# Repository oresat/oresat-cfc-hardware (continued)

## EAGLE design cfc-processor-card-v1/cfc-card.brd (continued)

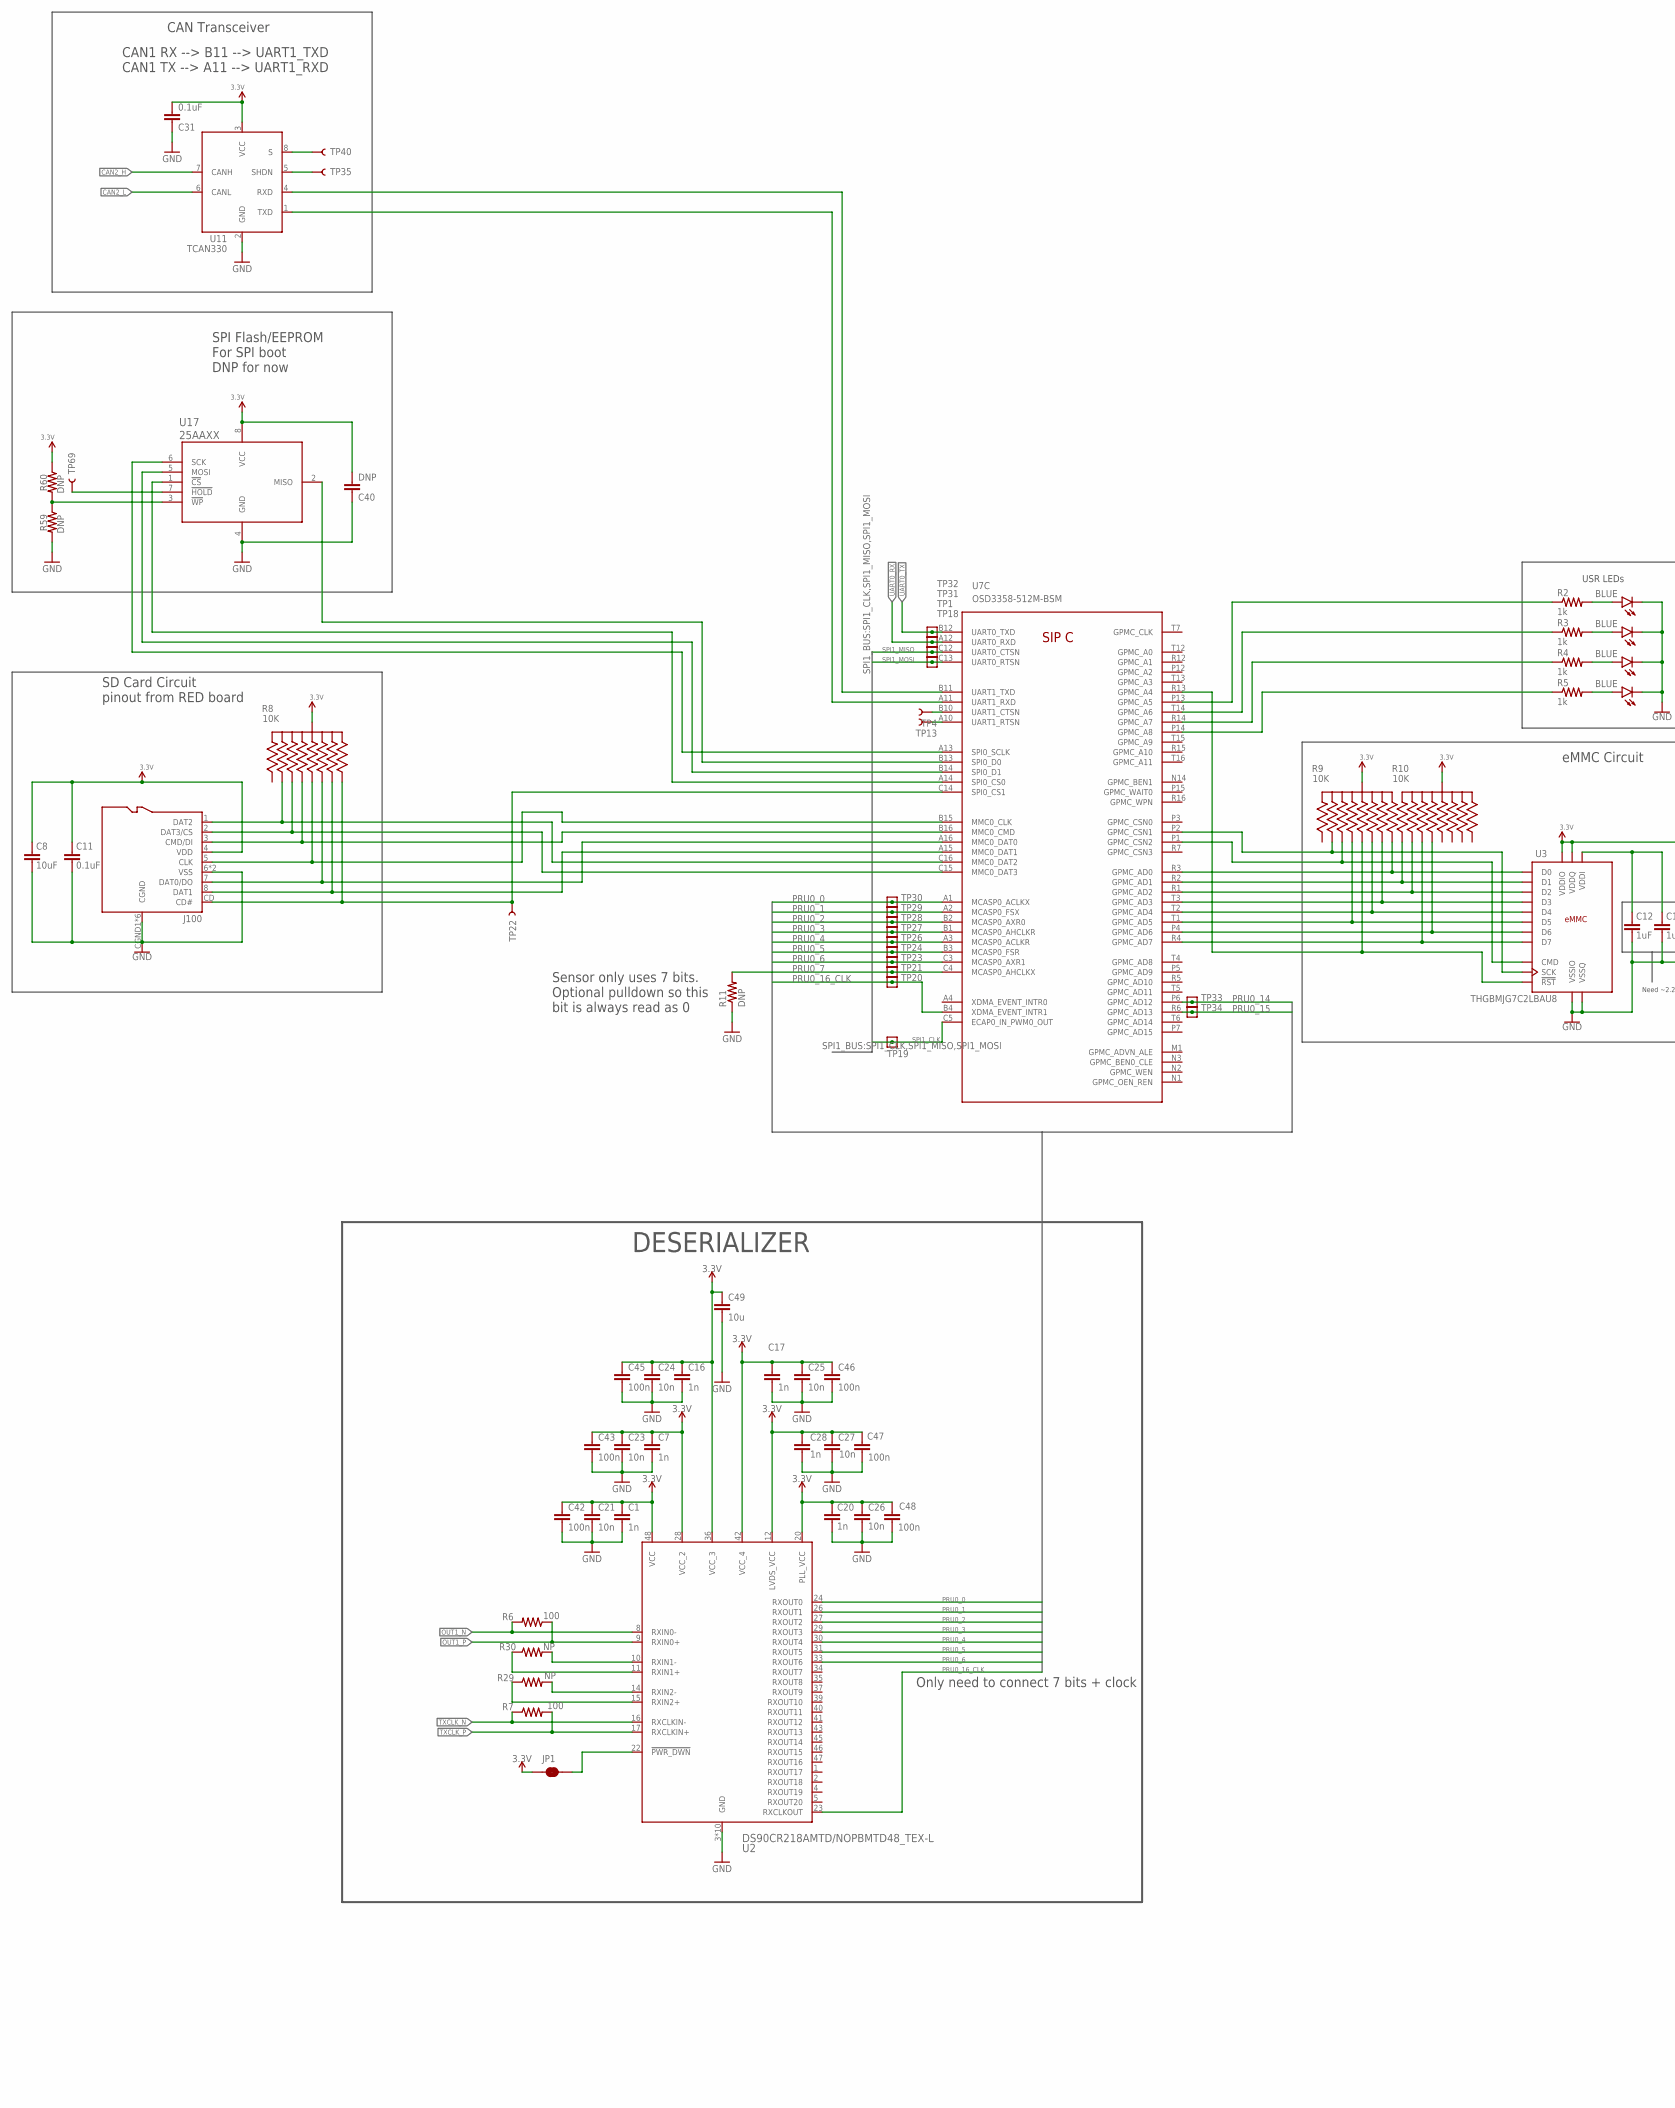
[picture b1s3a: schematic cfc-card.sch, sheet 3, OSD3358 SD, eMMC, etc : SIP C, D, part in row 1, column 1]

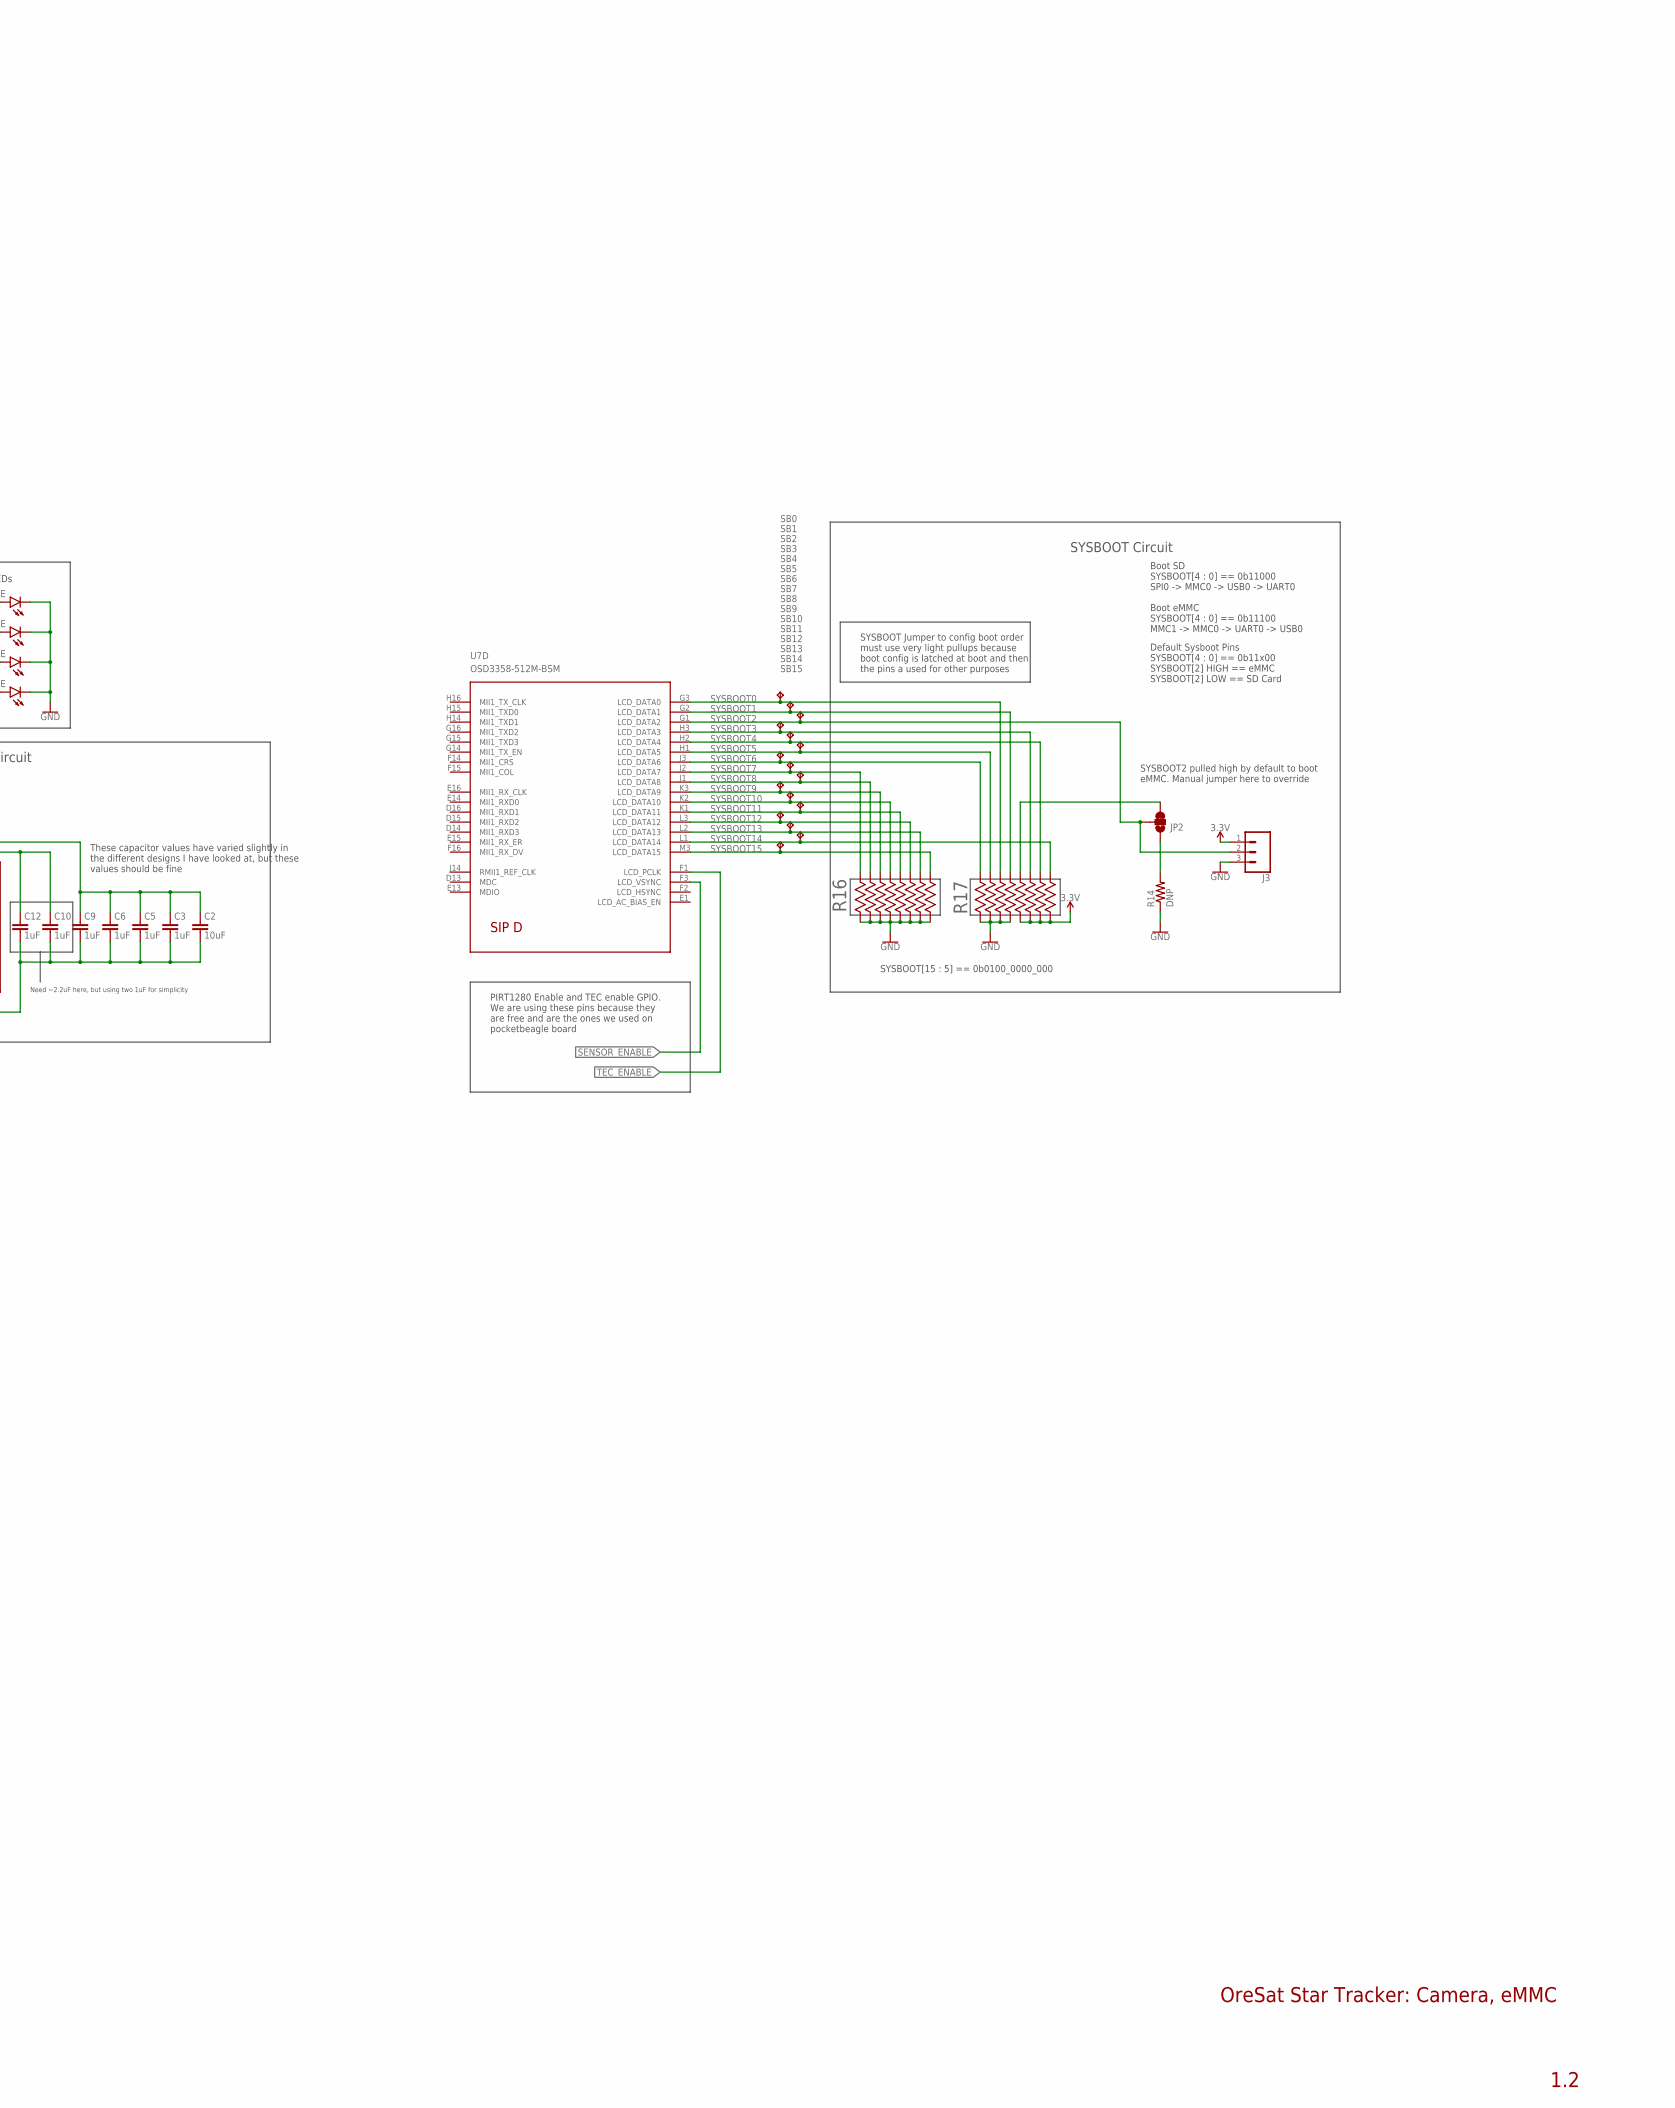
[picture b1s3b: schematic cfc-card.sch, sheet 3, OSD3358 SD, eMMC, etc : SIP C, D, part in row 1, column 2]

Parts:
C1, C7, C16, C17, C20, C28: 1n; .0402-C-NOSILK; MPN GRM155R71H102KA01J
C2, C8: 10uF; .0805-B
C3, C5, C6, C9, C10, C12: 1uF; .0603-A
C11, C31: 0.1uF; .0603-A
C21, C23, C24, C25, C26, C27: 10n; .0402-C-NOSILK; MPN C0603C103M5RACTU
C40: DNP; .0603-A
C42, C43, C45, C46, C47, C48: 100n; .0402-C-NOSILK; MPN C0805C104Z5VACTU
C49: 10u; .0603-C-NOSILK; MPN GRM188R61A106KE69J
D2, D3, D4, D5: BLUE; LED-0603
J3: CONN_03LONGPADS; 1X03_LONGPADS
J100: DM3BT-DSF-PEJS
JP1: JUMPER-SMT_2_NC_TRACE_SILK; SMT-JUMPER_2_NC_TRACE_SILK
JP2: JUMPER-SMT_3_1-NC_TRACE_SILK; SMT-JUMPER_3_1-NC_TRACE_SILK
R2, R3, R4, R5: 1k; .0603-A
R6, R7: 100; .0402-C-NOSILK; MPN RC0201FR-07100RL
R8, R9, R10: 10K; ARRAY_EXBA-M
R11, R14, R59, R60: DNP; .0603-A
R16, R17: 100k; RES_EXB2HV
R29, R30: NP; .0402-C-NOSILK; MPN RC0201FR-07100RL
SB0, SB1, SB2, SB3, SB4, SB5, SB6, SB7, SB8, SB9, SB10, SB11, SB12, SB13, SB14, SB15: TEST-POINT-SMALL
TP1, TP18, TP19, TP20, TP21, TP23, TP24, TP26, TP27, TP28, TP29, TP30, TP31, TP32, TP33, TP34: TEST-POINT; 2MM-TEST-POINT
TP4, TP13, TP22, TP35, TP40, TP69: TEST-POINT3X4; PAD.03X.04
U2: DS90CR218AMTD/NOPBMTD48_TEX-L; MTD48_TEX-L
U3: THGBMJG7C2LBAU8; BGA-153(11.5X13)(EMMC-BA); MPN THGBMJG7C2LBAU8
U7: OSD3358-512M-BSM; OSD335X-BGA-256
U11: TCAN330; SOT23-8_TI-DCN
U17: 25AAXX; SOIC8

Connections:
3.3V: C1.1, C2.1, C3.1, C5.1, C6.1, C7.1, C8.1, C9.1, C11.1, C16.1, C17.1, C20.1, C21.1, C23.1, C24.1, C25.1, C26.1, C27.1, C28.1, C31.2, C40.2, C42.1, C43.1, C45.1, C46.1, C47.1, C48.1, C49.1, J3.1, J100.4 (VDD), JP1.1, R8.5 (55), R8.10 (55), R9.5 (55), R9.10 (55), R10.5 (55), R10.10 (55), R17.5, R17.6, R17.7, R17.8, R60.1, U2.12 (LVDS_VCC), U2.20 (PLL_VCC), U2.28 (VCC_2), U2.36 (VCC_3), U2.42 (VCC_4), U2.48 (VCC), U3.C6 (VDDQ), U3.E6 (VDDIO), U3.F5 (VDDIO), U3.J10 (VDDIO), U3.K9 (VDDIO), U3.M4 (VDDQ), U3.N4 (VDDQ), U3.P3 (VDDQ), U3.P5 (VDDQ), U11.3 (VCC), U17.8 (VCC); also elsewhere on the board
!EMMC_RST: R9.3 (33), U3.K5 (!RST!), U7.R13 (GPMC_A4)
!PWR_DWN: JP1.2, U2.22 (!PWR_DWN)
CAN2_H: U11.7 (CANH); also elsewhere on the board
CAN2_L: U11.6 (CANL); also elsewhere on the board
EMMC_CLK: R9.9 (99), U3.M6 (SCK), U7.P2 (GPMC_CSN1)
EMMC_CMD: R9.2 (22), U3.M5 (CMD), U7.P1 (GPMC_CSN2)
EMMC_DAT0: R9.6 (66), U3.A3 (D0), U7.R3 (GPMC_AD0)
EMMC_DAT1: R10.1 (11), U3.A4 (D1), U7.R2 (GPMC_AD1)
EMMC_DAT2: R10.9 (99), U3.A5 (D2), U7.R1 (GPMC_AD2)
EMMC_DAT3: R9.4 (44), U3.B2 (D3), U7.T3 (GPMC_AD3)
EMMC_DAT4: R9.7 (77), U3.B3 (D4), U7.T2 (GPMC_AD4)
EMMC_DAT5: R9.8 (88), U3.B4 (D5), U7.T1 (GPMC_AD5)
EMMC_DAT6: R10.8 (88), U3.B5 (D6), U7.P4 (GPMC_AD6)
EMMC_DAT7: R10.2 (22), U3.B6 (D7), U7.R4 (GPMC_AD7)
GND: C1.2, C2.2, C3.2, C5.2, C6.2, C7.2, C8.2, C9.2, C10.2, C11.2, C12.2, C16.2, C17.2, C20.2, C21.2, C23.2, C24.2, C25.2, C26.2, C27.2, C28.2, C31.1, C40.1, C42.2, C43.2, C45.2, C46.2, C47.2, C48.2, C49.2, D2.C, D3.C, D4.C, D5.C, J3.3, J100.6 (VSS), J100.CGND1 (CGND), J100.CGND2 (CGND), J100.CGND3 (CGND), J100.CGND4 (CGND), J100.CGND5 (CGND), J100.CGND6 (CGND), J100.GND (VSS), R11.1, R14.1, R16.1, R16.2, R16.3, R16.4, R16.5, R16.6, R16.7, R16.8, R17.1, R17.2, R17.3, R17.4, R59.2, U2.3 (GND), U2.7 (GND), U2.13 (GND), U2.18 (GND), U2.19 (GND), U2.21 (GND), U2.25 (GND), U2.32 (GND), U2.38 (GND), U2.44 (GND), U3.A6 (VSSIO), U3.C4 (VSSQ), U3.E7 (VSSIO), U3.G5 (VSSIO), U3.H10 (VSSIO), U3.J5 (VSSIO), U3.K8 (VSSIO), U3.N2 (VSSQ), U3.N5 (VSSQ), U3.P4 (VSSQ), U3.P6 (VSSQ), U11.2 (GND), U17.4 (GND); also elsewhere on the board
unnamed: JP2.1, R14.2
unnamed: D5.A, R5.2
unnamed: R29.2, U2.14 (RXIN2-)
unnamed: J100.1 (DAT2), R8.9 (99), U7.C16 (MMC0_DAT2)
unnamed: J100.2 (DAT3/CS), R8.2 (22), U7.C15 (MMC0_DAT3)
unnamed: J100.3 (CMD/DI), R8.8 (88), U7.B16 (MMC0_CMD)
unnamed: J100.5 (CLK), R8.3 (33), U7.B15 (MMC0_CLK)
unnamed: J100.8 (DAT1), R8.4 (44), U7.A15 (MMC0_DAT1)
unnamed: J100.CD (CD#), R8.6 (66), TP22.P$1, U7.C14 (SPI0_CS1)
unnamed: U7.B11 (UART1_TXD), U11.4 (RXD)
unnamed: U7.A11 (UART1_RXD), U11.1 (TXD)
unnamed: TP40.P$1, U11.8 (S)
unnamed: TP35.P$1, U11.5 (SHDN)
unnamed: J100.7 (DAT0/DO), R8.7 (77), U7.A16 (MMC0_DAT0)
unnamed: JP2.3, R17.12
unnamed: TP4.P$1, U7.B10 (UART1_CTSN)
unnamed: U7.A13 (SPI0_SCLK), U17.6 (SCK)
unnamed: U7.B13 (SPI0_D0), U17.2 (MISO)
unnamed: U7.B14 (SPI0_D1), U17.5 (MOSI)
unnamed: U7.A14 (SPI0_CS0), U17.1 (!CS)
unnamed: R29.1, U2.15 (RXIN2+)
unnamed: R30.2, U2.10 (RXIN1-)
unnamed: R30.1, U2.11 (RXIN1+)
unnamed: D4.A, R4.2
unnamed: D3.A, R3.2
unnamed: D2.A, R2.2
unnamed: R59.1, R60.2, U17.3 (!WP)
unnamed: TP69.P$1, U17.7 (!HOLD)
unnamed: TP13.P$1, U7.A10 (UART1_RTSN)
unnamed: C10.1, C12.1, U3.C2 (VDDI)
unnamed: R2.1, U7.P13 (GPMC_A5)
unnamed: R3.1, U7.T14 (GPMC_A6)
unnamed: R4.1, U7.R14 (GPMC_A7)
unnamed: R5.1, U7.P14 (GPMC_A8)
OUT1_N: R6.2, U2.8 (RXIN0-); also elsewhere on the board
OUT1_P: R6.1, U2.9 (RXIN0+); also elsewhere on the board
PRU0_0: TP30.1, U2.24 (RXOUT0), U7.A1 (MCASP0_ACLKX)
PRU0_1: TP29.1, U2.26 (RXOUT1), U7.A2 (MCASP0_FSX)
PRU0_2: TP28.1, U2.27 (RXOUT2), U7.B2 (MCASP0_AXR0)
PRU0_3: TP27.1, U2.29 (RXOUT3), U7.B1 (MCASP0_AHCLKR)
PRU0_4: TP26.1, U2.30 (RXOUT4), U7.A3 (MCASP0_ACLKR)
PRU0_5: TP24.1, U2.31 (RXOUT5), U7.B3 (MCASP0_FSR)
PRU0_6: TP23.1, U2.33 (RXOUT6), U7.C3 (MCASP0_AXR1)
PRU0_7: R11.2, TP21.1, U7.C4 (MCASP0_AHCLKX)
PRU0_14: TP33.1, U7.P6 (GPMC_AD12)
PRU0_15: TP34.1, U7.R6 (GPMC_AD13)
PRU0_16_CLK: TP20.1, U2.23 (RXCLKOUT), U7.B4 (XDMA_EVENT_INTR1)
SENSOR_ENABLE: U7.F3 (LCD_VSYNC); also elsewhere on the board
SPI1_CLK: TP19.1, U7.C5 (ECAP0_IN_PWM0_OUT); also elsewhere on the board
SPI1_MISO: TP1.1, U7.C12 (UART0_CTSN); also elsewhere on the board
SPI1_MOSI: TP18.1, U7.C13 (UART0_RTSN); also elsewhere on the board
SYSBOOT0: R17.14, SB0.TP, U7.G3 (LCD_DATA0)
SYSBOOT1: R17.13, SB1.TP, U7.G2 (LCD_DATA1)
SYSBOOT2: J3.2, JP2.2, SB2.TP, U7.G1 (LCD_DATA2); also elsewhere on the board
SYSBOOT3: R17.11, SB3.TP, U7.H3 (LCD_DATA3)
SYSBOOT4: R17.10, SB4.TP, U7.H2 (LCD_DATA4)
SYSBOOT5: R17.15, SB5.TP, U7.H1 (LCD_DATA5)
SYSBOOT6: R17.16, SB6.TP, U7.J3 (LCD_DATA6)
SYSBOOT7: R16.16, SB7.TP, U7.J2 (LCD_DATA7)
SYSBOOT8: R16.15, SB8.TP, U7.J1 (LCD_DATA8)
SYSBOOT9: R16.14, SB9.TP, U7.K3 (LCD_DATA9)
SYSBOOT10: R16.13, SB10.TP, U7.K2 (LCD_DATA10)
SYSBOOT11: R16.12, SB11.TP, U7.K1 (LCD_DATA11)
SYSBOOT12: R16.11, SB12.TP, U7.L3 (LCD_DATA12)
SYSBOOT13: R16.10, SB13.TP, U7.L2 (LCD_DATA13)
SYSBOOT14: R17.9, SB14.TP, U7.L1 (LCD_DATA14)
SYSBOOT15: R16.9, SB15.TP, U7.M3 (LCD_DATA15)
TEC_ENABLE: U7.F1 (LCD_PCLK); also elsewhere on the board
TXCLK_N: R7.1, U2.16 (RXCLKIN-); also elsewhere on the board
TXCLK_P: R7.2, U2.17 (RXCLKIN+); also elsewhere on the board
UART0_RX: TP31.1, U7.A12 (UART0_RXD); also elsewhere on the board
UART0_TX: TP32.1, U7.B12 (UART0_TXD); also elsewhere on the board

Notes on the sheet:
SYSBOOT Jumper to config boot order must use very light pullups because boot config is latched at boot and then the pins a used for other purposes
SYSBOOT[15 : 5] == 0b0100_0000_000
Boot SD SYSBOOT[4 : 0] == 0b11000 SPI0 -> MMC0 -> USB0 -> UART0 Boot eMMC SYSBOOT[4 : 0] == 0b11100 MMC1 -> MMC0 -> UART0 -> USB0
USR LEDs
These capacitor values have varied slightly in the different designs I have looked at, but these values should be fine
eMMC Circuit
SD Card Circuit pinout from RED board
SYSBOOT Circuit
CAN Transceiver
CAN1 RX --> B11 --> UART1_TXD CAN1 TX --> A11 --> UART1_RXD
Need ~2.2uF here, but using two 1uF for simplicity
Default Sysboot Pins SYSBOOT[4 : 0] == 0b11x00 SYSBOOT[2] HIGH == eMMC SYSBOOT[2] LOW == SD Card
SPI Flash/EEPROM For SPI boot DNP for now
OreSat Star Tracker: Camera, eMMC
1.2
Only need to connect 7 bits + clock
DESERIALIZER
Sensor only uses 7 bits. Optional pulldown so this bit is always read as 0
PIRT1280 Enable and TEC enable GPIO. We are using these pins because they are free and are the ones we used on pocketbeagle board
SYSBOOT2 pulled high by default to boot eMMC. Manual jumper here to override

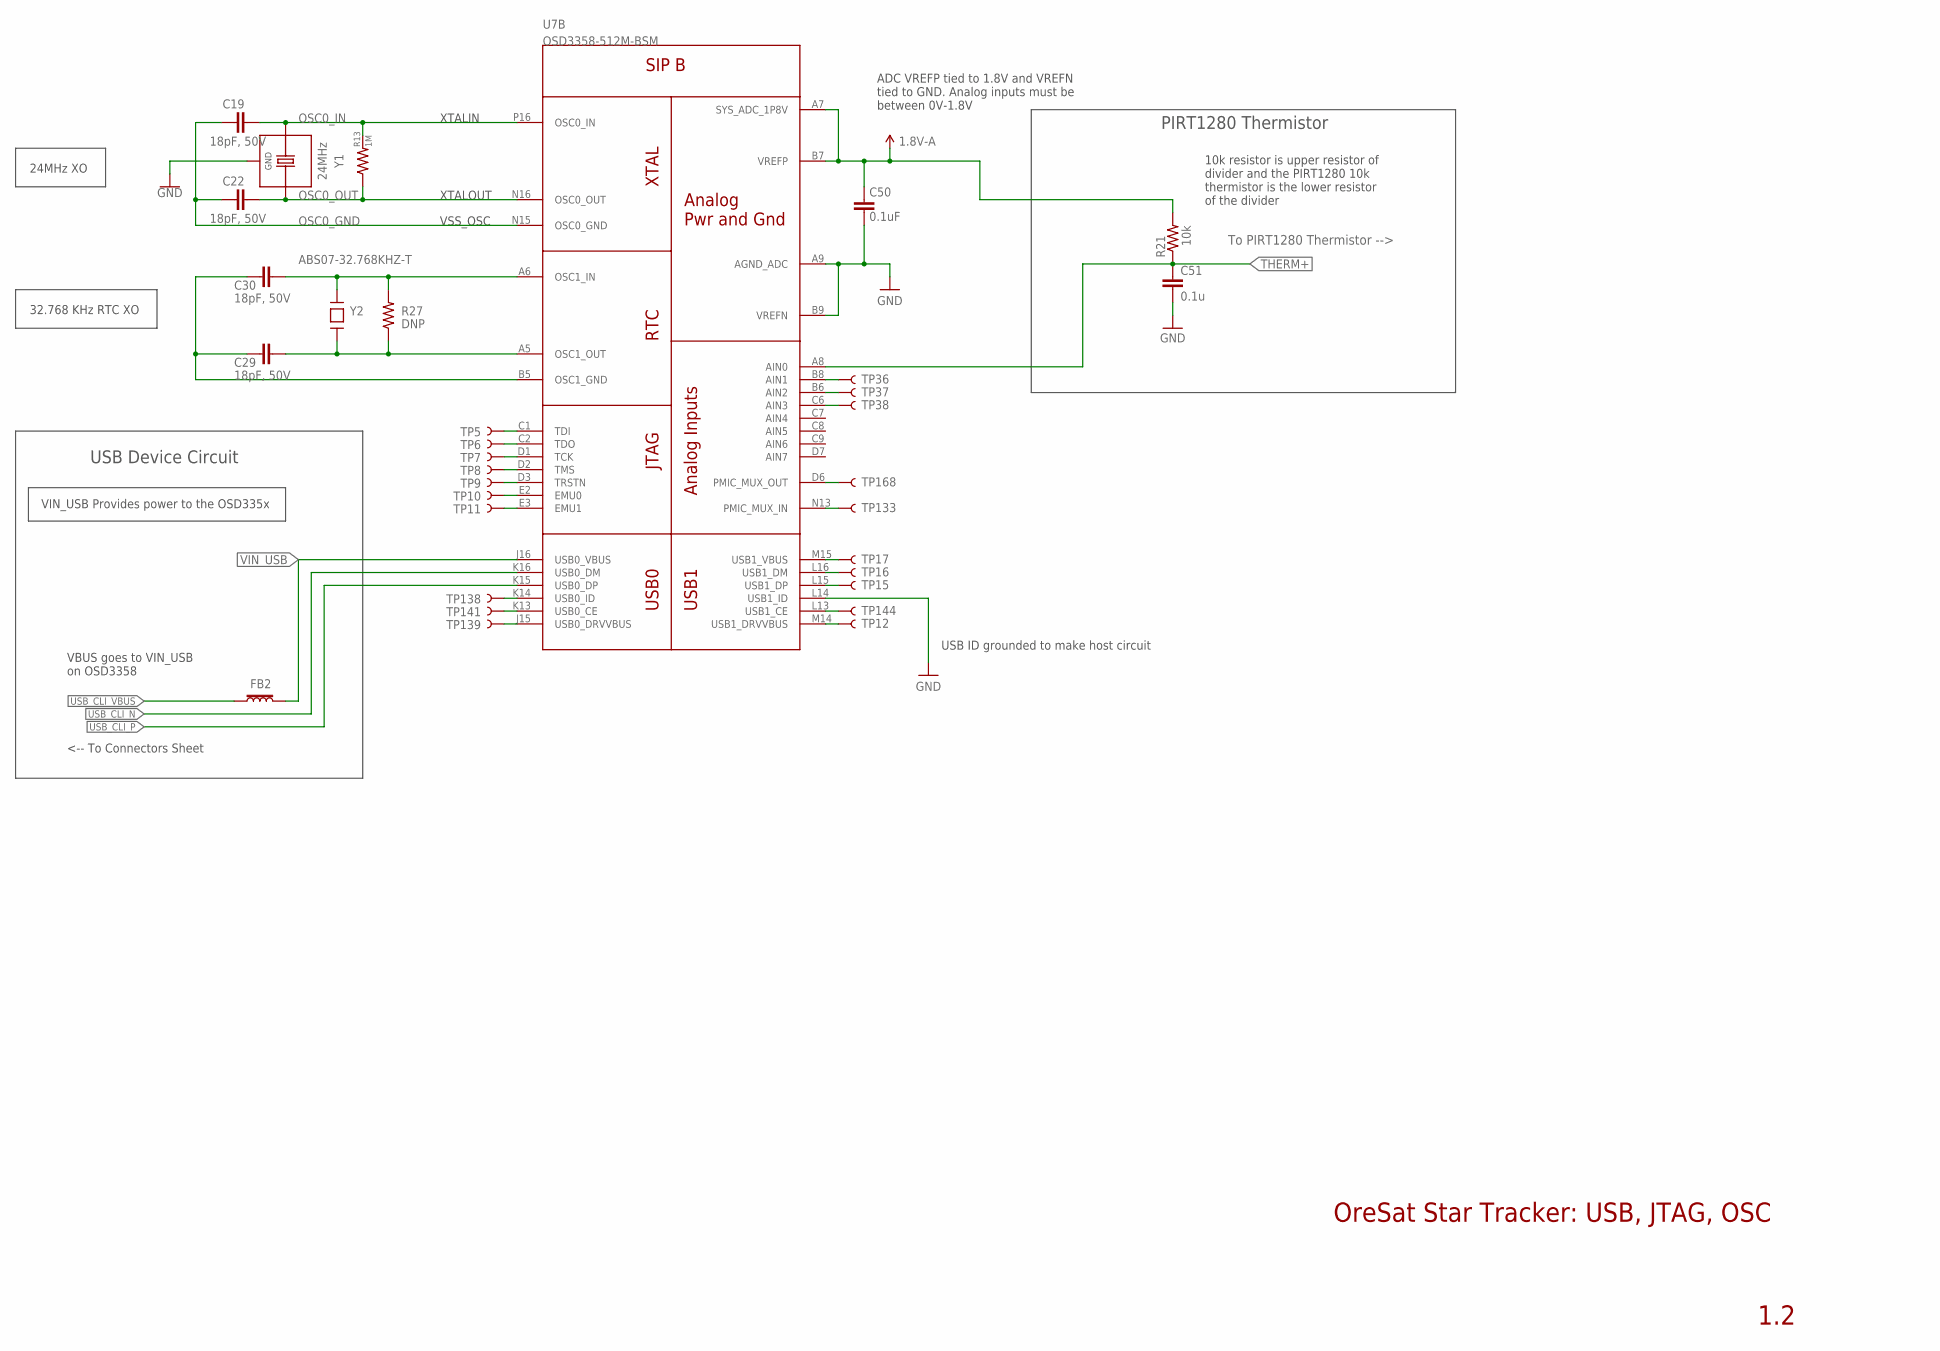
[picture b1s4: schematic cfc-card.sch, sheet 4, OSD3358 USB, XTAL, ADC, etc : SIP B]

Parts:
C19, C22, C29, C30: 18pF, 50V; .0603-A
C50: 0.1uF; .0603-A
C51: 0.1u; .0603-A
FB2: 30Ω/1.8A; 0603; MPN BLM18KG300JH1D
R13: 1M; .0603-A
R21: 10k; .0603-A
R27: DNP; .0603-A
TP5, TP6, TP7, TP8, TP9, TP10, TP11, TP12, TP15, TP16, TP17, TP36, TP37, TP38, TP133, TP138, TP139, TP141, TP144, TP168: TEST-POINT3X4; PAD.03X.04
U7: OSD3358-512M-BSM; OSD335X-BGA-256
Y1: 24MHz; 5X3.2-4SMD
Y2: ABS07-32.768KHZ-T; CRYSTAL_3.2X1.5

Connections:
1.8V-A: C50.1, R21.2, U7.A7 (SYS_ADC_1P8V), U7.B7 (VREFP)
GND: C50.2, C51.2, U7.A9 (AGND_ADC), U7.B9 (VREFN), U7.L14 (USB1_ID), Y1.2 (GND), Y1.4 (GND); also elsewhere on the board
unnamed: TP11.P$1, U7.E3 (EMU1)
unnamed: TP10.P$1, U7.E2 (EMU0)
unnamed: TP9.P$1, U7.D3 (TRSTN)
unnamed: TP8.P$1, U7.D2 (TMS)
unnamed: TP7.P$1, U7.D1 (TCK)
unnamed: TP36.P$1, U7.B8 (AIN1)
unnamed: TP37.P$1, U7.B6 (AIN2)
unnamed: TP38.P$1, U7.C6 (AIN3)
unnamed: TP141.P$1, U7.K13 (USB0_CE)
unnamed: TP139.P$1, U7.J15 (USB0_DRVVBUS)
unnamed: TP168.P$1, U7.D6 (PMIC_MUX_OUT)
unnamed: TP6.P$1, U7.C2 (TDO)
unnamed: TP144.P$1, U7.L13 (USB1_CE)
unnamed: TP5.P$1, U7.C1 (TDI)
unnamed: TP15.P$1, U7.L15 (USB1_DP)
unnamed: TP138.P$1, U7.K14 (USB0_ID)
unnamed: TP12.P$1, U7.M14 (USB1_DRVVBUS)
unnamed: TP16.P$1, U7.L16 (USB1_DM)
unnamed: TP17.P$1, U7.M15 (USB1_VBUS)
OSC0_GND: C19.1, C22.1, U7.N15 (OSC0_GND)
OSC0_IN: C19.2, R13.2, U7.P16 (OSC0_IN), Y1.1 (X1)
OSC0_OUT: C22.2, R13.1, U7.N16 (OSC0_OUT), Y1.3 (X2)
OSC1_GND1: C29.2, C30.2, U7.B5 (OSC1_GND)
OSC1_IN1: C30.1, R27.2, U7.A6 (OSC1_IN), Y2.P$2
OSC1_OUT1: C29.1, R27.1, U7.A5 (OSC1_OUT), Y2.P$1
PMIC_MUX_IN: TP133.P$1, U7.N13 (PMIC_MUX_IN)
THERM+: C51.1, R21.1, U7.A8 (AIN0); also elsewhere on the board
USB_CLI_N: U7.K16 (USB0_DM); also elsewhere on the board
USB_CLI_P: U7.K15 (USB0_DP); also elsewhere on the board
USB_CLI_VBUS: FB2.1; also elsewhere on the board
VIN_USB: FB2.2, U7.J16 (USB0_VBUS); also elsewhere on the board

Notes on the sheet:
VBUS goes to VIN_USB on OSD3358
USB Device Circuit
24MHz XO
<-- To Connectors Sheet
XTALIN
XTALOUT
VSS_OSC
VIN_USB Provides power to the OSD335x
OreSat Star Tracker: USB, JTAG, OSC
1.2
USB ID grounded to make host circuit
ADC VREFP tied to 1.8V and VREFN tied to GND. Analog inputs must be between 0V-1.8V
To PIRT1280 Thermistor -->
10k resistor is upper resistor of divider and the PIRT1280 10k thermistor is the lower resistor of the divider
PIRT1280 Thermistor
32.768 KHz RTC XO

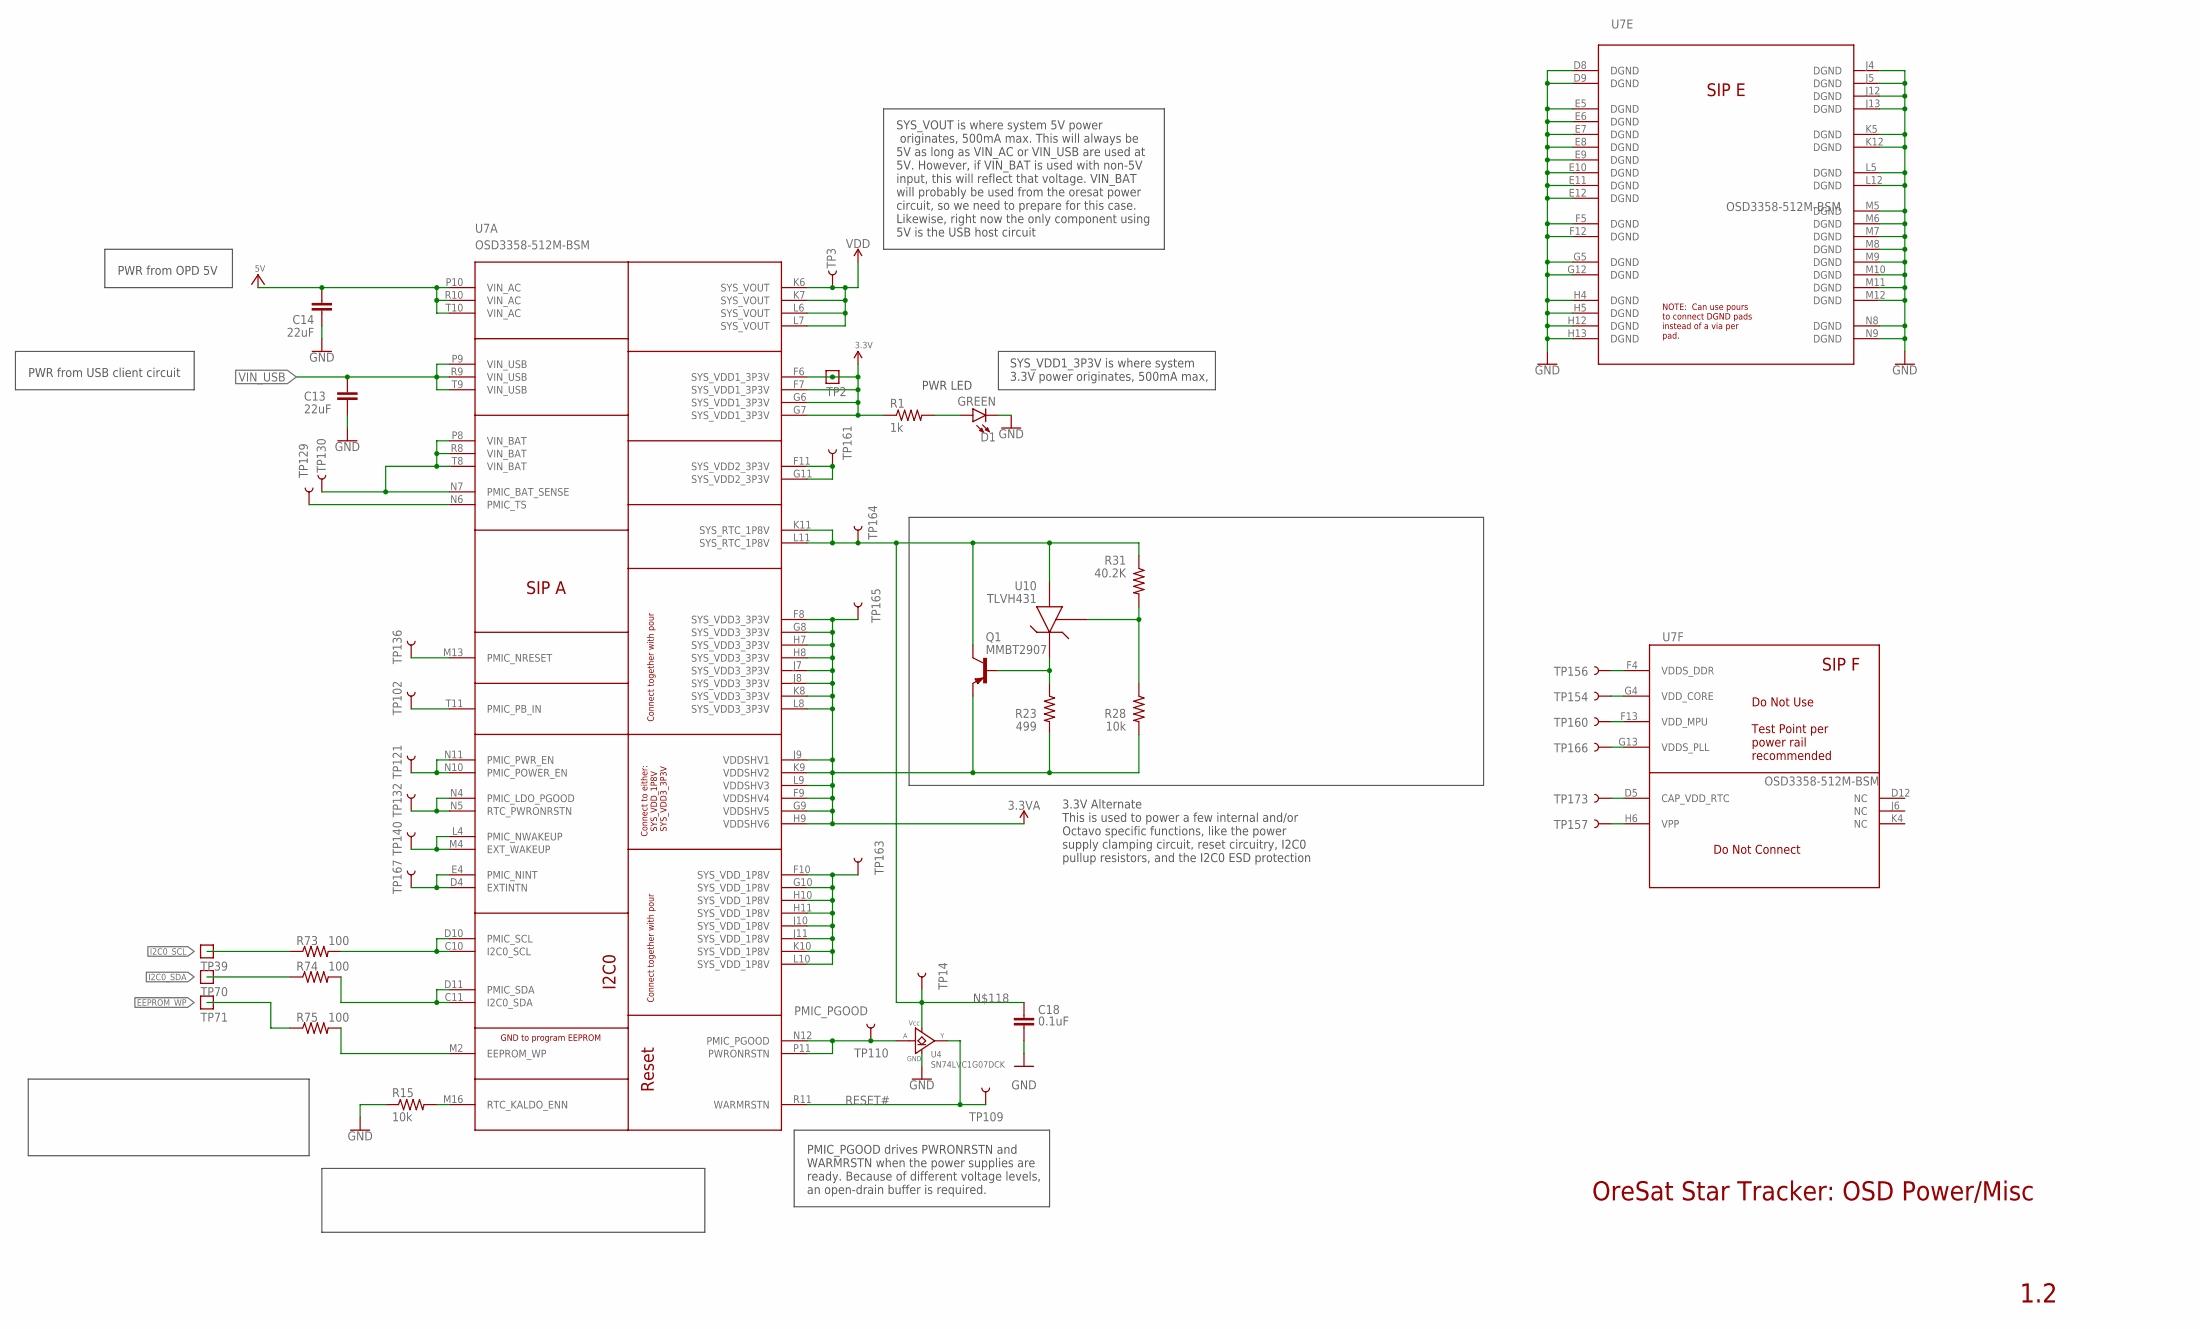
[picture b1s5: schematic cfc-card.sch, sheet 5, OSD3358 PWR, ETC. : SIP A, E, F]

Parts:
C13, C14: 22uF; C1210
C18: 0.1uF; .0603-A
D1: GREEN; LED-0603
Q1: MMBT2907; SOT23-BEC
R1: 1k; .0603-A
R15, R28: 10k; .0603-A
R23: 499; .0603-A
R31: 40.2K; .0603-A
R73, R74, R75: 100; .0603-A
TP2, TP39, TP70, TP71: TEST-POINT; 2MM-TEST-POINT
TP3, TP14, TP102, TP109, TP110, TP121, TP129, TP130, TP132, TP136, TP140, TP154, TP156, TP157, TP160, TP161, TP163, TP164, TP165, TP166, TP167, TP173: TEST-POINT3X4; PAD.03X.04
U4: SN74LVC1G07DCK; C70(TI-DCK)
U7: OSD3358-512M-BSM; OSD335X-BGA-256
U10: TLVH431; SOT23-3

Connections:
3.3V: R1.1, TP2.1, U7.F6 (SYS_VDD1_3P3V), U7.F7 (SYS_VDD1_3P3V), U7.G6 (SYS_VDD1_3P3V), U7.G7 (SYS_VDD1_3P3V); also elsewhere on the board
3.3VA: Q1.E, R23.2, R28.2, TP165.P$1, U7.F8 (SYS_VDD3_3P3V), U7.F9 (VDDSHV4), U7.G8 (SYS_VDD3_3P3V), U7.G9 (VDDSHV5), U7.H7 (SYS_VDD3_3P3V), U7.H8 (SYS_VDD3_3P3V), U7.H9 (VDDSHV6), U7.J7 (SYS_VDD3_3P3V), U7.J8 (SYS_VDD3_3P3V), U7.J9 (VDDSHV1), U7.K8 (SYS_VDD3_3P3V), U7.K9 (VDDSHV2), U7.L8 (SYS_VDD3_3P3V), U7.L9 (VDDSHV3)
5V: C14.1, U7.P10 (VIN_AC), U7.R10 (VIN_AC), U7.T10 (VIN_AC); also elsewhere on the board
EEPROM_WP: R75.1, TP71.1; also elsewhere on the board
GND: C13.2, C14.2, C18.2, D1.C, R15.1, U4.3 (GND), U7.D8 (DGND), U7.D9 (DGND), U7.E5 (DGND), U7.E6 (DGND), U7.E7 (DGND), U7.E8 (DGND), U7.E9 (DGND), U7.E10 (DGND), U7.E11 (DGND), U7.E12 (DGND), U7.F5 (DGND), U7.F12 (DGND), U7.G5 (DGND), U7.G12 (DGND), U7.H4 (DGND), U7.H5 (DGND), U7.H12 (DGND), U7.H13 (DGND), U7.J4 (DGND), U7.J5 (DGND), U7.J12 (DGND), U7.J13 (DGND), U7.K5 (DGND), U7.K12 (DGND), U7.L5 (DGND), U7.L12 (DGND), U7.M5 (DGND), U7.M6 (DGND), U7.M7 (DGND), U7.M8 (DGND), U7.M9 (DGND), U7.M10 (DGND), U7.M11 (DGND), U7.M12 (DGND), U7.N8 (DGND), U7.N9 (DGND); also elsewhere on the board
I2C0_SCL: R73.1, TP39.1; also elsewhere on the board
I2C0_SDA: R74.1, TP70.1; also elsewhere on the board
unnamed: R28.1, R31.2, U10.1 (REF)
unnamed: Q1.B, R23.1, U10.2 (CATHODE)
unnamed: TP157.P$1, U7.H6 (VPP)
unnamed: TP173.P$1, U7.D5 (CAP_VDD_RTC)
unnamed: TP166.P$1, U7.G13 (VDDS_PLL)
unnamed: TP160.P$1, U7.F13 (VDD_MPU)
unnamed: TP154.P$1, U7.G4 (VDD_CORE)
unnamed: TP156.P$1, U7.F4 (VDDS_DDR)
unnamed: D1.A, R1.2
unnamed: R74.2, U7.C11 (I2C0_SDA), U7.D11 (PMIC_SDA)
unnamed: R75.2, U7.M2 (EEPROM_WP)
unnamed: R73.2, U7.C10 (I2C0_SCL), U7.D10 (PMIC_SCL)
unnamed: C18.1, Q1.C, R31.1, TP14.P$1, TP164.P$1, U4.5 (VCC), U7.K11 (SYS_RTC_1P8V), U7.L11 (SYS_RTC_1P8V), U10.3 (ANODE)
unnamed: TP130.P$1, U7.N7 (PMIC_BAT_SENSE), U7.P8 (VIN_BAT), U7.R8 (VIN_BAT), U7.T8 (VIN_BAT)
unnamed: TP129.P$1, U7.N6 (PMIC_TS)
unnamed: TP161.P$1, U7.F11 (SYS_VDD2_3P3V), U7.G11 (SYS_VDD2_3P3V)
unnamed: TP163.P$1, U7.F10 (SYS_VDD_1P8V), U7.G10 (SYS_VDD_1P8V), U7.H10 (SYS_VDD_1P8V), U7.H11 (SYS_VDD_1P8V), U7.J10 (SYS_VDD_1P8V), U7.J11 (SYS_VDD_1P8V), U7.K10 (SYS_VDD_1P8V), U7.L10 (SYS_VDD_1P8V)
unnamed: TP167.P$1, U7.D4 (EXTINTN), U7.E4 (PMIC_NINT)
unnamed: TP140.P$1, U7.L4 (PMIC_NWAKEUP), U7.M4 (EXT_WAKEUP)
unnamed: TP132.P$1, U7.N4 (PMIC_LDO_PGOOD), U7.N5 (RTC_PWRONRSTN)
unnamed: TP121.P$1, U7.N10 (PMIC_POWER_EN), U7.N11 (PMIC_PWR_EN)
unnamed: TP102.P$1, U7.T11 (PMIC_PB_IN)
unnamed: TP136.P$1, U7.M13 (PMIC_NRESET)
unnamed: R15.2, U7.M16 (RTC_KALDO_ENN)
PMIC_PGOOD: TP110.P$1, U4.2 (A), U7.N12 (PMIC_PGOOD), U7.P11 (PWRONRSTN)
RESET#: TP109.P$1, U4.4 (Y), U7.R11 (WARMRSTN)
VDD: TP3.P$1, U7.K6 (SYS_VOUT), U7.K7 (SYS_VOUT), U7.L6 (SYS_VOUT), U7.L7 (SYS_VOUT); also elsewhere on the board
VIN_USB: C13.1, U7.P9 (VIN_USB), U7.R9 (VIN_USB), U7.T9 (VIN_USB); also elsewhere on the board

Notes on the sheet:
SYS_VOUT is where system 5V power originates, 500mA max. This will always be 5V as long as VIN_AC or VIN_USB are used at 5V. However, if VIN_BAT is used with non-5V input, this will reflect that voltage. VIN_BAT will probably be used from the oresat power circuit, so we need to prepare for this cas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
SYS_VDD1_3P3V is where system 3.3V power originates, 500mA max,
PWR LED
PMIC_PGOOD drives PWRONRSTN and WARMRSTN when the power supplies are ready. Because of different voltage levels, an open-drain buffer is required.
PWR from USB client circuit
3.3V Alternate This is used to power a few internal and/or Octavo specific functions, like the power supply clamping circuit, reset circuitry, I2C0 pullup resistors, and the I2C0 ESD protection
OreSat Star Tracker: OSD Power/Misc
1.2
PWR from OPD 5V
